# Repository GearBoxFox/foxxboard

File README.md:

## Foxxboard: A Wireless, split ergonomic keyboard for normal keyboard users
---
This keyboard was inspired by the Lily85 keyboard layout, keeping a more standard 64 key layout while also gaining the bonus ergonomics of a split keyboard. I designed it to be a multi purpose keyboard, ergonomic for typing while still having access to all the needed keys for competitive gaming. I also decided to build it wirelessly so I can easily take and use it with my laptop on the go.

*insert final image here*

# Features
- 64 key layout
- 4 key thumb cluster per side
- BLE wireless support using nice!nano v2
- Traditional pinky row using 1.5u keys
- Low profile using Gateron ks33 switches 
- 2x nice!view for low powered HUD
- Custom firmware written in RMK using Rust :ferrisyippee: 

## > [!NOTE]
> The firmware for the display module is still a WIP, but I'm talking with the head RMK dev 
> to get it fully running. The firmware bundled with this has parts of a display demo, and my 
> hackpad has a working display in RMK.

# PCB

# Renders

# BOM 

## > [!NOTE]
> I plan on printing my own case.
>
> I also need to double check prices on things as there have almost certainly been price changes.

| Name                 | Qty | Price             |
|----------------------|-----|-------------------|
| PCB                  | 5   | $14.59 w/shipping |
| GLP ks33 Banana      | 64  | $21.48 w/shipping |
| THT 1N4148 Diodes    | 64  | Hackclub          |
| EC11 Encoder         | 2   | $2.00 AliExpress  |
| Clone Nice!Nano V2   | 2   | $5.42 AliExpress  |
| GLP Hot-swap sockets | 100 | $8.42 AliExpress  |
| 0.91" OLED Display   | 2   | $3.20 AliExpress  |
| 3.7v LiPo Battery    | 2   | $6.00             |
| EVQ-P7C01P Switch    | 2   | $0.56 Digikey     |

| Supplier    | Price (+ Shipping) | 
|-------------|--------------------|
| JLCPCB      | $14.59             |
| Keebio      | $22.48             |
| AliExpress  | $20.20             |
| Typeractive | $10.90             |
| Total       | $68.17             |

| Extras               | Qty | Price            |
|----------------------|-----|------------------|
| Nice!View            | 2   | $40              |
| True Nice!Nano V2    | 2   | $50              |

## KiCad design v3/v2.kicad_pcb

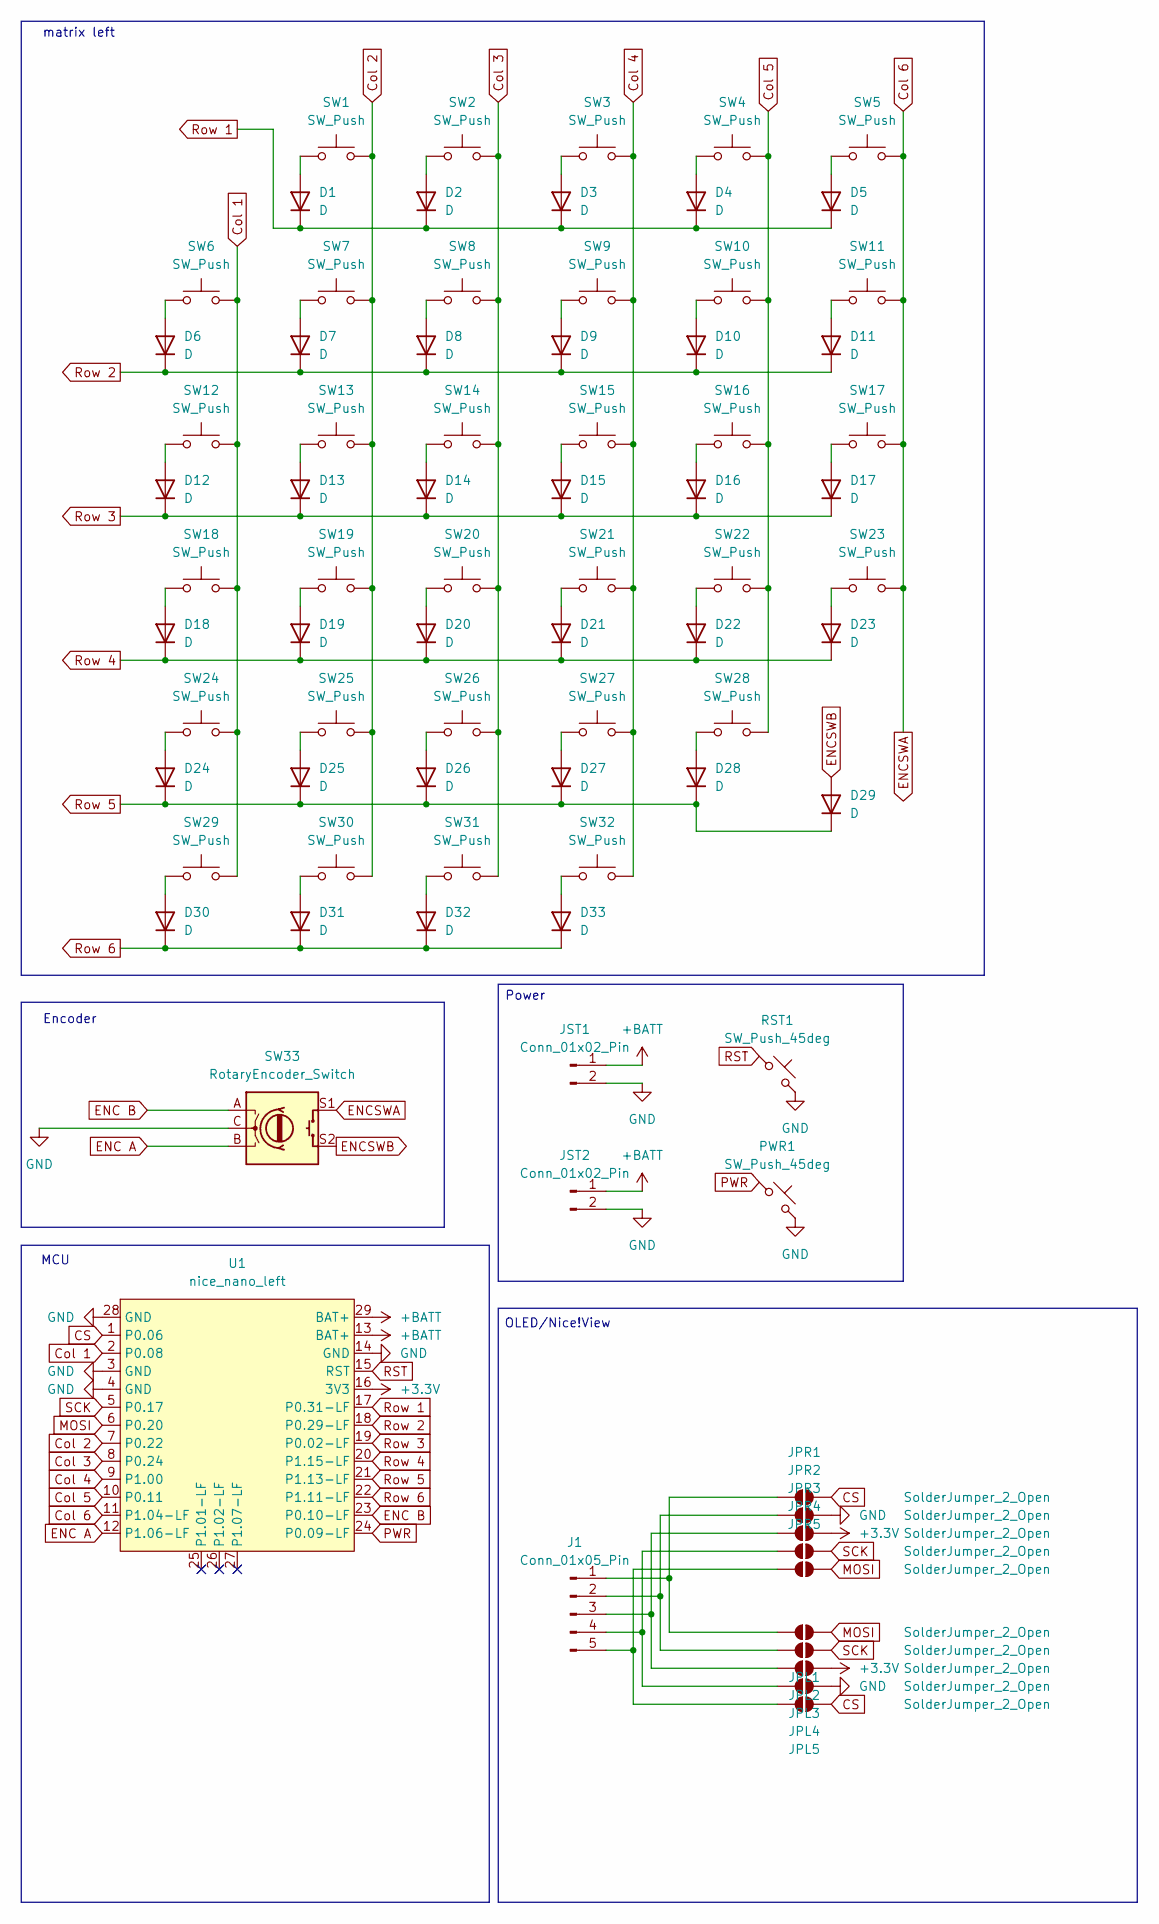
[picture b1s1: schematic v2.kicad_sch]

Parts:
D1, D2, D3, D4, D5, D6, D7, D8, D9, D10, D11, D12, D13, D14, D15, D16, D17, D18, D19, D20, D21, D22, D23, D24, D25, D26, D27, D28, D29, D30, D31, D32, D33: D; Diode-dual
J1: Conn_01x05_Pin; PinHeader_1x05_P2.54mm_Vertical
JPL1, JPL2, JPL3, JPL4, JPL5: SolderJumper_2_Open; SolderJumper-2_P1.3mm_Open_RoundedPad1.0x1.5mm
JPR1, JPR2, JPR3, JPR4, JPR5: SolderJumper_2_Open; SolderJumper-2_P1.3mm_Open_RoundedPad1.0x1.5mm
JST1, JST2: Conn_01x02_Pin; JST_PH_S2B-PH-K_1x02_P2.00mm_Horizontal
PWR1: SW_Push_45deg; EVQ-P7C-Reversible
RST1: SW_Push_45deg; EVQ-P7C-Reversible
SW1, SW2, SW3, SW4, SW5, SW6, SW7, SW8, SW9, SW10, SW11, SW12, SW13, SW14, SW15, SW16, SW17, SW18, SW19, SW20, SW21, SW22, SW23, SW24, SW25, SW26, SW27, SW28, SW29, SW30, SW31, SW32: SW_Push; gateron-ks27-hotswap-reversible
SW33: RotaryEncoder_Switch; RotaryEncoder_EC11
U1: nice_nano_left; nice_nano_AH_Reversible

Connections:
+3.3V: JPL3.2 (B), JPR3.2 (B), U1.16 (3V3)
+BATT: JST1.1, JST2.1, U1.13 (BAT+), U1.29 (BAT+)
CS: JPL5.2 (B), JPR1.2 (B), U1.1 (P0.06)
Col 1: SW6.2, SW12.2, SW18.2, SW24.2, SW29.2, U1.2 (P0.08)
Col 2: SW1.2, SW7.2, SW13.2, SW19.2, SW25.2, SW30.2, U1.7 (P0.22)
Col 3: SW2.2, SW8.2, SW14.2, SW20.2, SW26.2, SW31.2, U1.8 (P0.24)
Col 4: SW3.2, SW9.2, SW15.2, SW21.2, SW27.2, SW32.2, U1.9 (P1.00)
Col 5: SW4.2, SW10.2, SW16.2, SW22.2, SW28.2, U1.10 (P0.11)
Col 6: SW5.2, SW11.2, SW17.2, SW23.2, SW33.S1, U1.11 (P1.04-LF)
ENC A: SW33.B, U1.12 (P1.06-LF)
ENC B: SW33.A, U1.23 (P0.10-LF)
ENCSWB: D29.2 (A), SW33.S2
GND: JPL4.2 (B), JPR2.2 (B), JST1.2, JST2.2, PWR1.2, RST1.2, SW33.C, U1.3 (GND), U1.4 (GND), U1.14 (GND), U1.28 (GND)
MOSI: JPL1.2 (B), JPR5.2 (B), U1.6 (P0.20)
unnamed: D1.2 (A), SW1.1
unnamed: D2.2 (A), SW2.1
unnamed: D3.2 (A), SW3.1
unnamed: D4.2 (A), SW4.1
unnamed: D5.2 (A), SW5.1
unnamed: D6.2 (A), SW6.1
unnamed: D7.2 (A), SW7.1
unnamed: D8.2 (A), SW8.1
unnamed: D9.2 (A), SW9.1
unnamed: D10.2 (A), SW10.1
unnamed: D11.2 (A), SW11.1
unnamed: D12.2 (A), SW12.1
unnamed: D13.2 (A), SW13.1
unnamed: D14.2 (A), SW14.1
unnamed: D15.2 (A), SW15.1
unnamed: D16.2 (A), SW16.1
unnamed: D17.2 (A), SW17.1
unnamed: D18.2 (A), SW18.1
unnamed: D19.2 (A), SW19.1
unnamed: D20.2 (A), SW20.1
unnamed: D21.2 (A), SW21.1
unnamed: D22.2 (A), SW22.1
unnamed: D23.2 (A), SW23.1
unnamed: D24.2 (A), SW24.1
unnamed: D25.2 (A), SW25.1
unnamed: D26.2 (A), SW26.1
unnamed: D27.2 (A), SW27.1
unnamed: D28.2 (A), SW28.1
unnamed: D30.2 (A), SW29.1
unnamed: D31.2 (A), SW30.1
unnamed: D32.2 (A), SW31.1
unnamed: D33.2 (A), SW32.1
unnamed: J1.1, JPL1.1 (A), JPR1.1 (A)
unnamed: J1.2, JPL2.1 (A), JPR2.1 (A)
unnamed: J1.3, JPL3.1 (A), JPR3.1 (A)
unnamed: J1.4, JPL4.1 (A), JPR4.1 (A)
unnamed: J1.5, JPL5.1 (A), JPR5.1 (A)
PWR: PWR1.1, U1.24 (P0.09-LF)
RST: RST1.1, U1.15 (RST)
Row 1: D1.1 (K), D2.1 (K), D3.1 (K), D4.1 (K), D5.1 (K), U1.17 (P0.31-LF)
Row 2: D6.1 (K), D7.1 (K), D8.1 (K), D9.1 (K), D10.1 (K), D11.1 (K), U1.18 (P0.29-LF)
Row 3: D12.1 (K), D13.1 (K), D14.1 (K), D15.1 (K), D16.1 (K), D17.1 (K), U1.19 (P0.02-LF)
Row 4: D18.1 (K), D19.1 (K), D20.1 (K), D21.1 (K), D22.1 (K), D23.1 (K), U1.20 (P1.15-LF)
Row 5: D24.1 (K), D25.1 (K), D26.1 (K), D27.1 (K), D28.1 (K), D29.1 (K), U1.21 (P1.13-LF)
Row 6: D30.1 (K), D31.1 (K), D32.1 (K), D33.1 (K), U1.22 (P1.11-LF)
SCK: JPL2.2 (B), JPR4.2 (B), U1.5 (P0.17)

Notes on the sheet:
MCU
Encoder
matrix left
Power
OLED/Nice!View

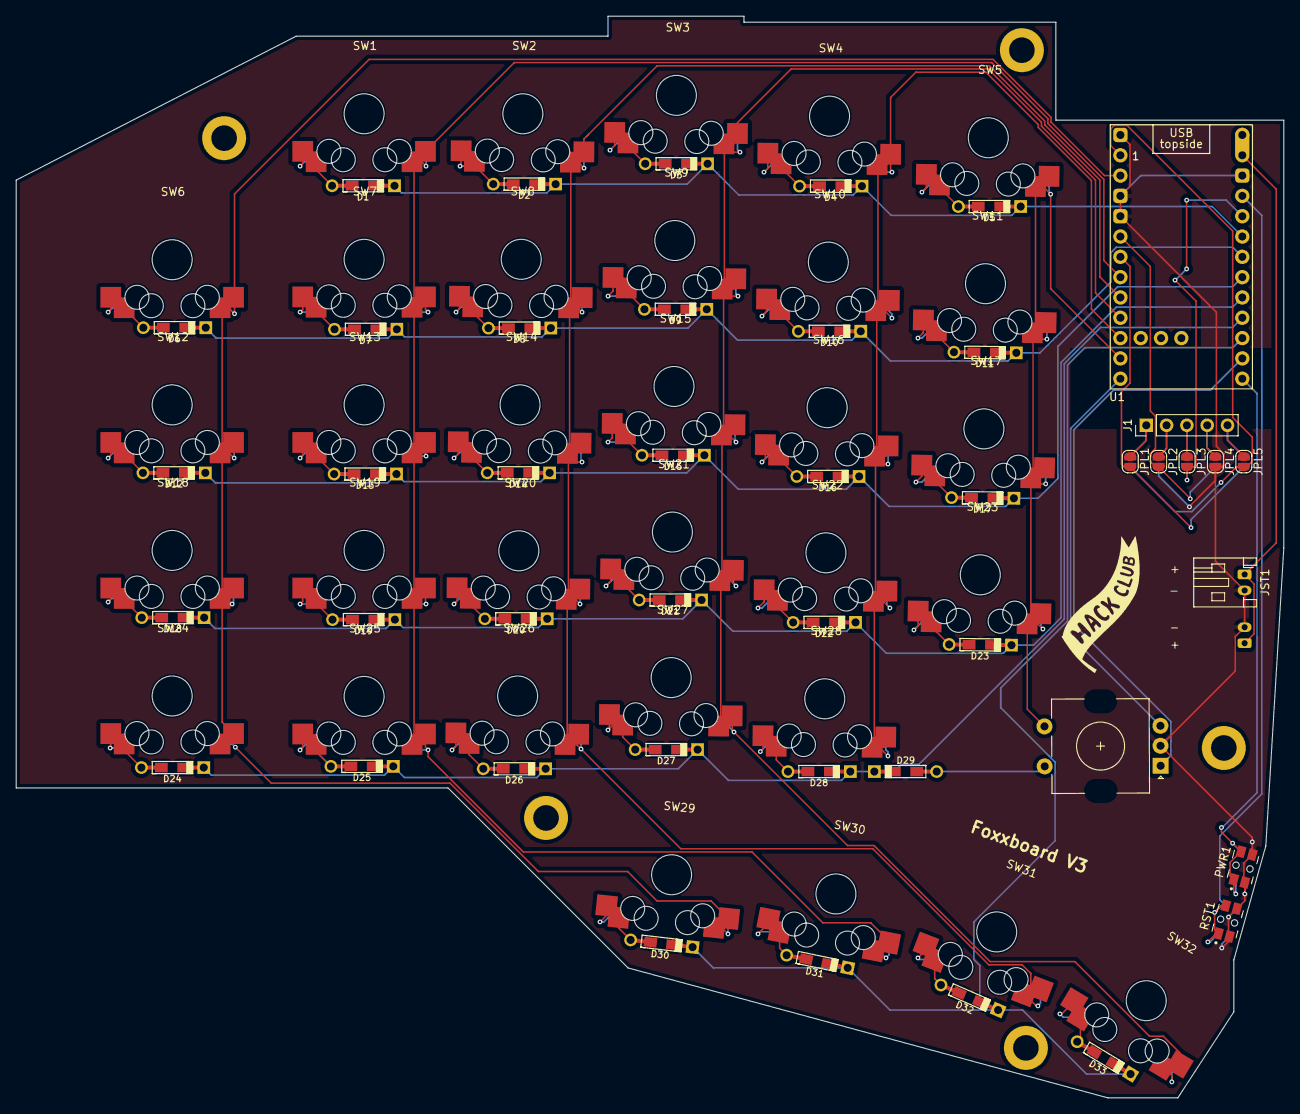
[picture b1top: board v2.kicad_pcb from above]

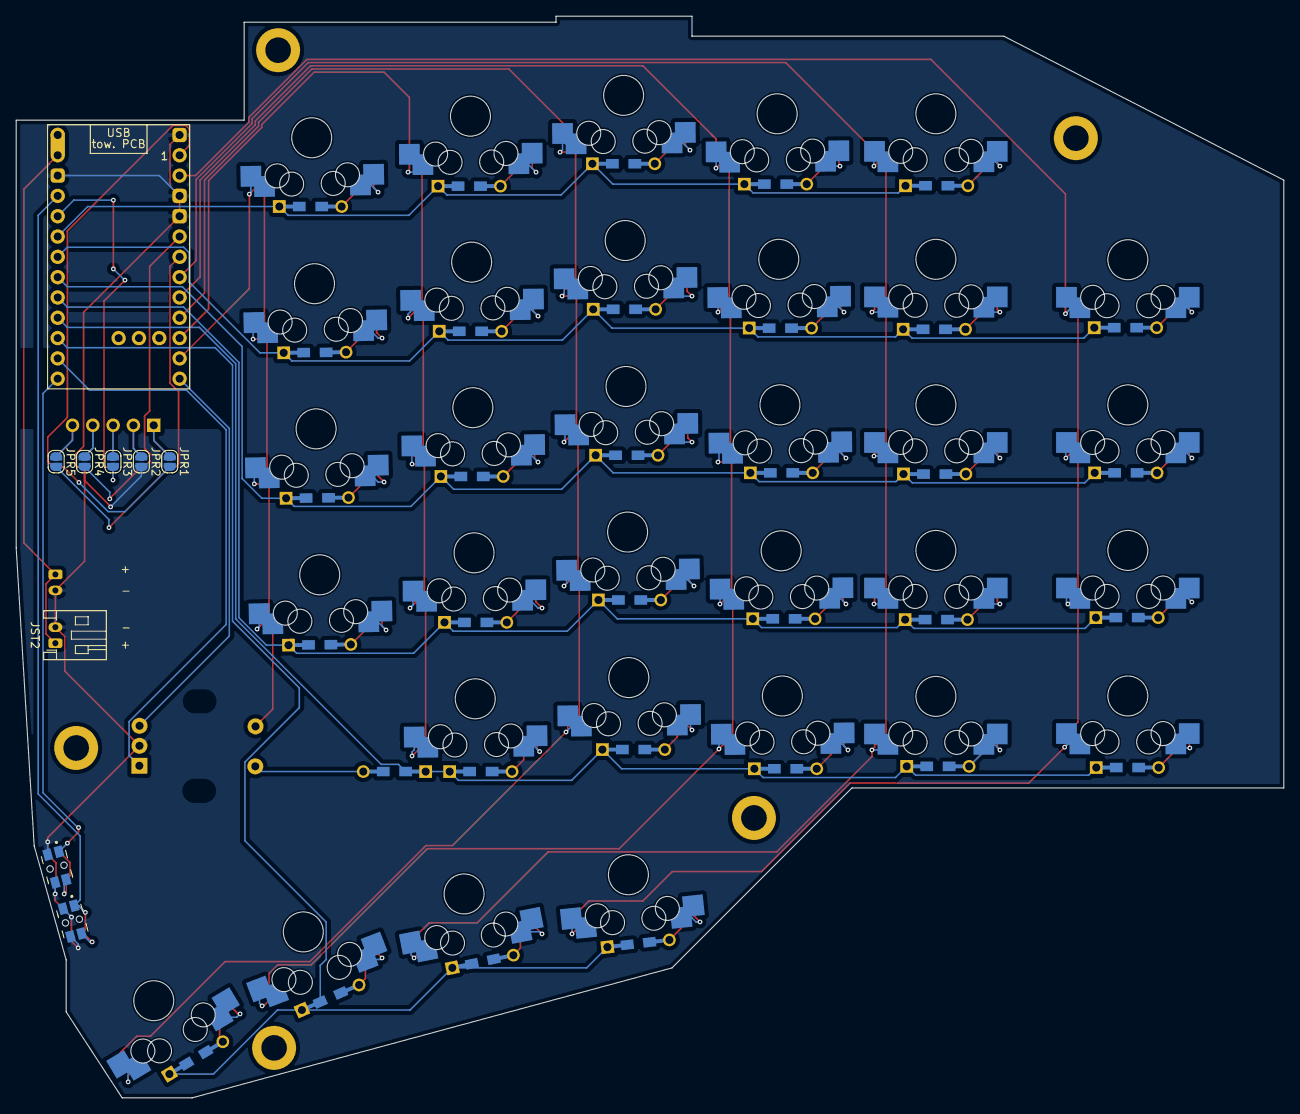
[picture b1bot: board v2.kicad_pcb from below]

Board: 2 copper layers, 158.5 x 135.2 mm, 82 parts (6 on the bottom side), 60 nets.

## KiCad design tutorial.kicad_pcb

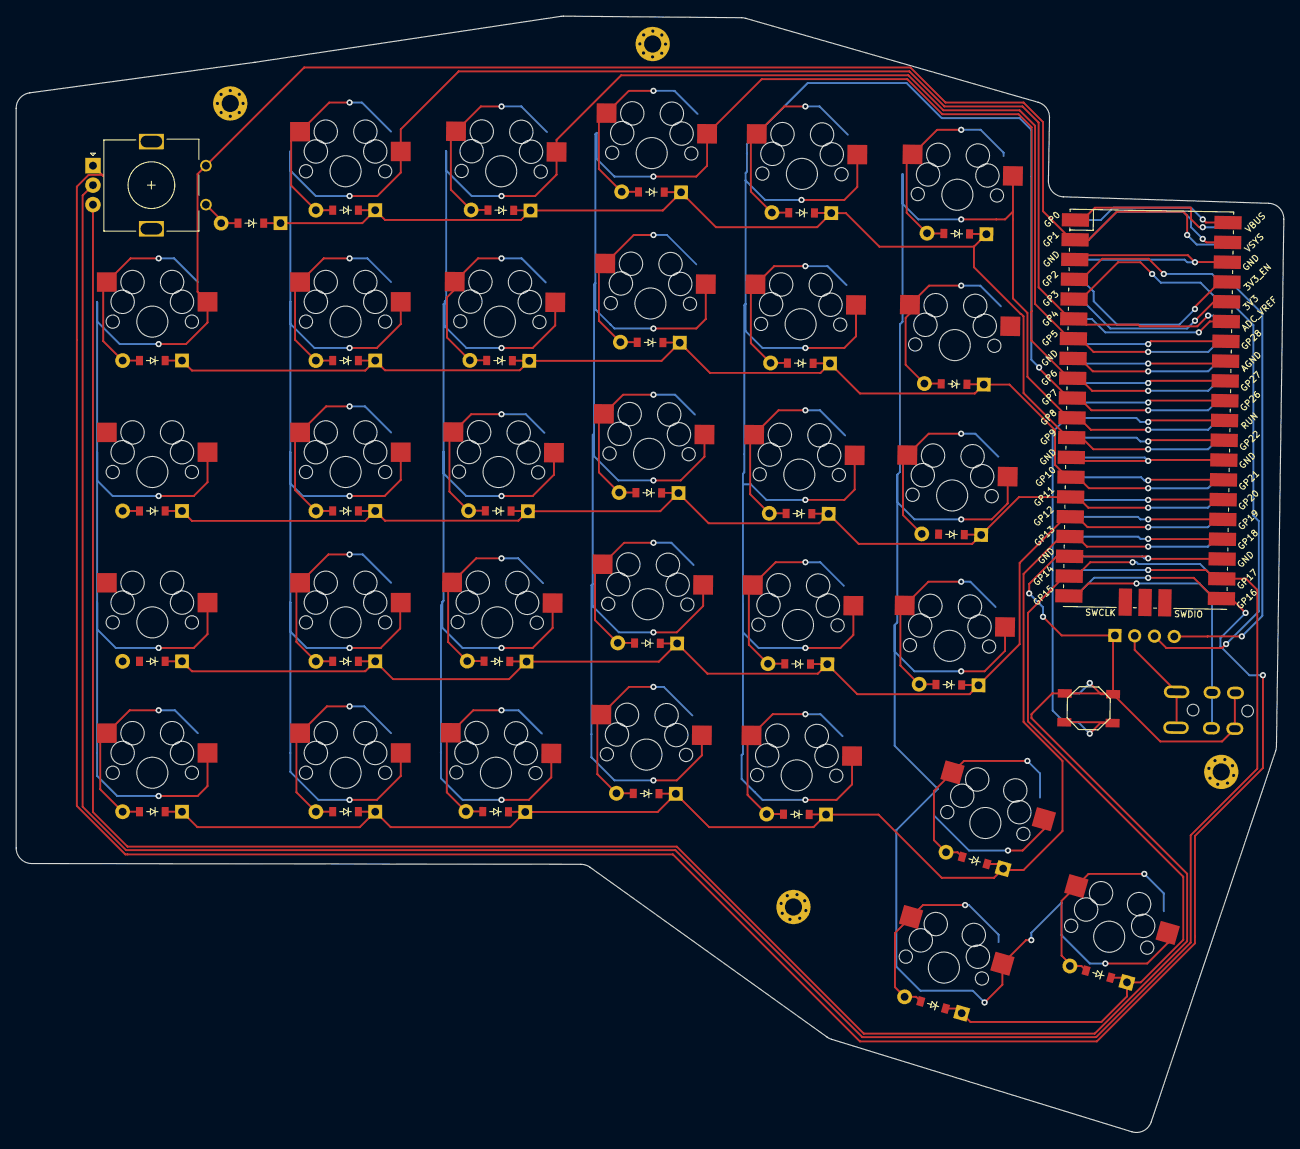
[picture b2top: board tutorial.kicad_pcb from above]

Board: 2 copper layers, 162.7 x 143.3 mm, 74 parts (0 on the bottom side), 67 nets.

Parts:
B1, B2: SW_TACT_ALPS_SKQGABE010
D1, D2, D3, D4, D4#2, D5, D6, D7, D8, D9, D10, D11, D12, D13, D14, D15, D16, D17, D18, D19, D20, D21, D22, D23, D24, D25, D26, D27, D28, D29, D30, D31: ComboDiode
OLED1: OLED; OLED_headers
ROT1: rotary_encoder
S1, S2, S3, S4, S5, S6, S7, S8, S9, S10, S11, S12, S13, S14, S15, S16, S17, S18, S19, S20, S21, S22, S23, S24, S25, S26, S27, S28, S29, S30, S31: MX
TRRS1: trrs_pj320a (reversible, symmetric)
_1, _1#2: RPi_Pico_SMD_TH
_2, _3, _4, _5: MountingHole_2.2mm_M2_Pad_Via

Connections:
3V3: _1.36, _1#2.36
3V3_EN: _1.37, _1#2.37
ADC_VREF: _1.35, _1#2.35
AGND: _1.33, _1#2.33
GND: B1.1, B2.1, OLED1.1, ROT1.B, TRRS1.2, _1.3, _1.8, _1.13, _1.18, _1.23, _1.28, _1.38, _1#2.3, _1#2.8, _1#2.13, _1#2.18, _1#2.23, _1#2.28, _1#2.38
GP0: _1.1, _1#2.1
GP1: ROT1.1, S1.1, S2.1, S3.1, S4.1, _1.2, _1#2.2
GP2: OLED1.4, _1.4, _1#2.4
GP3: OLED1.3, _1.5, _1#2.5
GP4: S5.1, S6.1, S7.1, S8.1, S9.1, _1.6, _1#2.6
GP5: S10.1, S11.1, S12.1, S13.1, S14.1, _1.7, _1#2.7
GP6: S15.1, S16.1, S17.1, S18.1, S19.1, _1.9, _1#2.9
GP7: S20.1, S21.1, S22.1, S23.1, S24.1, _1.10, _1#2.10
GP8: S25.1, S26.1, S27.1, S28.1, S29.1, S30.1, S31.1, _1.11, _1#2.11
GP9: D4.1, D9.1, D14.1, D19.1, D24.1, D28.1, _1.12, _1#2.12
GP10: D4#2.1, D8.1, D13.1, D18.1, D23.1, D27.1, _1.14, _1#2.14
GP11: D3.1, D7.1, D12.1, D17.1, D22.1, D26.1, _1.15, _1#2.15
GP12: D2.1, D6.1, D11.1, D16.1, D21.1, D25.1, _1.16, _1#2.16
GP13: D1.1, D5.1, D10.1, D15.1, D20.1, D30.1, _1.17, _1#2.17
GP14: D29.1, D31.1, _1.19, _1#2.19
GP15: TRRS1.3, _1.20, _1#2.20
GP16: ROT1.A, _1.21, _1#2.21
GP17: ROT1.C, _1.22, _1#2.22
GP18: _1.24, _1#2.24
GP19: _1.25, _1#2.25
GP20: _1.26, _1#2.26
GP21: _1.27, _1#2.27
GP22: _1.29, _1#2.29
GP26: _1.31, _1#2.31
GP27: _1.32, _1#2.32
GP28: _1.34, _1#2.34
RUN: B1.2, B2.2, _1.30, _1#2.30
VBUS: _1.40, _1#2.40
VCC: OLED1.2, TRRS1.4
VSYS: _1.39, _1#2.39
enc: D4.2, ROT1.2
index_bottom: D21.2, S21.2
index_home: D22.2, S22.2
index_mod: D20.2, S20.2
index_num: D24.2, S24.2
index_top: D23.2, S23.2
inner_bottom: D25.2, S25.2
inner_home: D26.2, S26.2
inner_num: D28.2, S28.2
inner_top: D27.2, S27.2
layer_cluster: D29.2, S29.2
layer_top: D30.2, S30.2
middle_bottom: D16.2, S16.2
middle_home: D17.2, S17.2
middle_mod: D15.2, S15.2
middle_num: D19.2, S19.2
middle_top: D18.2, S18.2
outer_bottom: D1.2, S1.2
outer_home: D2.2, S2.2
outer_num: D4#2.2, S4.2
outer_top: D3.2, S3.2
pinky_bottom: D6.2, S6.2
pinky_home: D7.2, S7.2
pinky_mod: D5.2, S5.2
pinky_num: D9.2, S9.2
pinky_top: D8.2, S8.2
ring_bottom: D11.2, S11.2
ring_home: D12.2, S12.2
ring_mod: D10.2, S10.2
ring_num: D14.2, S14.2
ring_top: D13.2, S13.2
space_cluster: D31.2, S31.2

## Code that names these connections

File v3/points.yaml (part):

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    autobind: 10
    skip: false
    asym: both
    colrow: pinky_mod
    name: matrix_pinky_mod
    zone: *ref_1
    col: *ref_2
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    autobind: 10
    skip: false
    asym: both
    colrow: pinky_bottom
    name: matrix_pinky_bottom
    zone: *ref_1
    col: *ref_2
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    autobind: 10
    skip: false
    asym: both
    colrow: pinky_home
    name: matrix_pinky_home
    zone: *ref_1
    col: *ref_2
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    autobind: 10
    skip: false
    asym: both
    colrow: pinky_top
    name: matrix_pinky_top
    zone: *ref_1
    col: *ref_2
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    autobind: 10
    skip: false
    asym: both
    colrow: pinky_num
    name: matrix_pinky_num
    zone: *ref_1
    col: *ref_2
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
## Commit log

2025-01-17 add project files
2025-01-17 added pico, moved parts around
2025-01-19 modified the pcb some
2025-01-19 fixed positioning for pico and trrs, added oled
2025-01-19 add reset buttons
2025-01-19 define pins
2025-01-20 ready to start routing
2025-01-20 attempt to set up routing
2025-01-20 routing setup done, now to actually route
2025-01-20 fix routing setup
2025-01-20 routing done!
2025-01-20 added an diode for the encoder
2025-01-20 run drc, get useless errors
2025-01-20 final YAML changes I didn't commit
2025-01-20 things are getting done
2025-01-20 removed unneeded files
2025-01-30 added lots of footprints I doubt I'll need
2025-01-31 get the right footprints finally
2025-01-31 started adding backlighting
2025-01-31 v2 layout ergogen
2025-01-31 did some layout using a plugin
2025-01-31 schematic finished + some pcb
2025-02-01 I screwed up some layout
2025-02-01 layout fix started
2025-02-02 started moving some of the keys into place
2025-02-03 finished layout for all components
2025-02-03 added custom dual side hybrid diode footprint
2025-02-03 started running traces
2025-02-03 done for tonight, more trace routing
2025-02-05 redo some schematics, time to redo LEDs
2025-02-05 fix LED placement
2025-02-05 finished routing and make fill zones
2025-02-05 remove fill zones
2025-02-07 added qmk powered logo
2025-02-07 import and export 3d models
2025-02-13 added qrcode and decals
2025-02-18 start v3 with nice!nano
2025-02-18 started adding the nice!nano footprints
2025-02-19 redo layout to use GLP low-profile
2025-02-19 redid footprints and layout for pcb
2025-02-19 start placing switches
2025-02-19 grid sizing right and other fun stuff
2025-02-19 added all needed labels
2025-02-19 place keyswitches
2025-02-19 reversible nice!nano
2025-02-19 finish routing all traces
2025-02-19 silkscreen
2025-02-19 added edge cuts and started cad again
2025-02-20 redo pcb export
2025-02-20 fix lots of reversible error stuff
2025-02-20 added branding
2025-02-20 added ground pads
2025-02-28 uhh nothing to pull so maybe an actual commit?
2025-03-09 update schematic files
2025-03-09 added firmware as submodule
2025-03-09 Update README to basic version
2025-03-09 add BOM to readme
2025-03-09 added total cost to BOM
2025-03-09 PCB cost
2025-03-10 Updated BOM with shipping costs
2025-03-10 Movethings into subdirectories
2025-03-10 added screenshots to readme
2025-03-10 added cad screenshots
2025-03-11 built firmware .uf2 files for production
